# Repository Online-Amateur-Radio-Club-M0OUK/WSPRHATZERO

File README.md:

# WSPRHATZERO

This is the schematics and PCB design for a small (Pi Zero) format Pi Hat that can transmit WSPR.

Designed to use the [QRP Labs](https://www.qrp-labs.com/lpfkit.html) Low Pass Filter kits to allow for interchangable drop in boards for different bands.

You should hold an appropriate Amateur Radio License and be aware of the legalities of the band/frequency transmission rules for your region before using this board.

## Software

The defaults from [Wsprry Pi](https://wsprry-pi.readthedocs.io/en/latest/) should work with this project.

Pin settings:
* LED - GPIO18
* Power - GPIO19

## BOM Ordering

There is a [Mouser compatible BOM](./Mouser%20BOM.xls) included in this repository.

## Credits

The original project and schematic was [WSPR Without Tears](https://files.tapr.org/product_docs/WSPR/TAPR%20-%20WSPR%20Without%20Tears%20-%20v2.2.pdf) by TAPR.

* Original prototyping and testing Eoin M0NVK.
* Schematic transcription and PCB Layout by [Tom 2E0JJI](https://blog.howrandom.net).
* Project inspiration from Vic EI5IYB.

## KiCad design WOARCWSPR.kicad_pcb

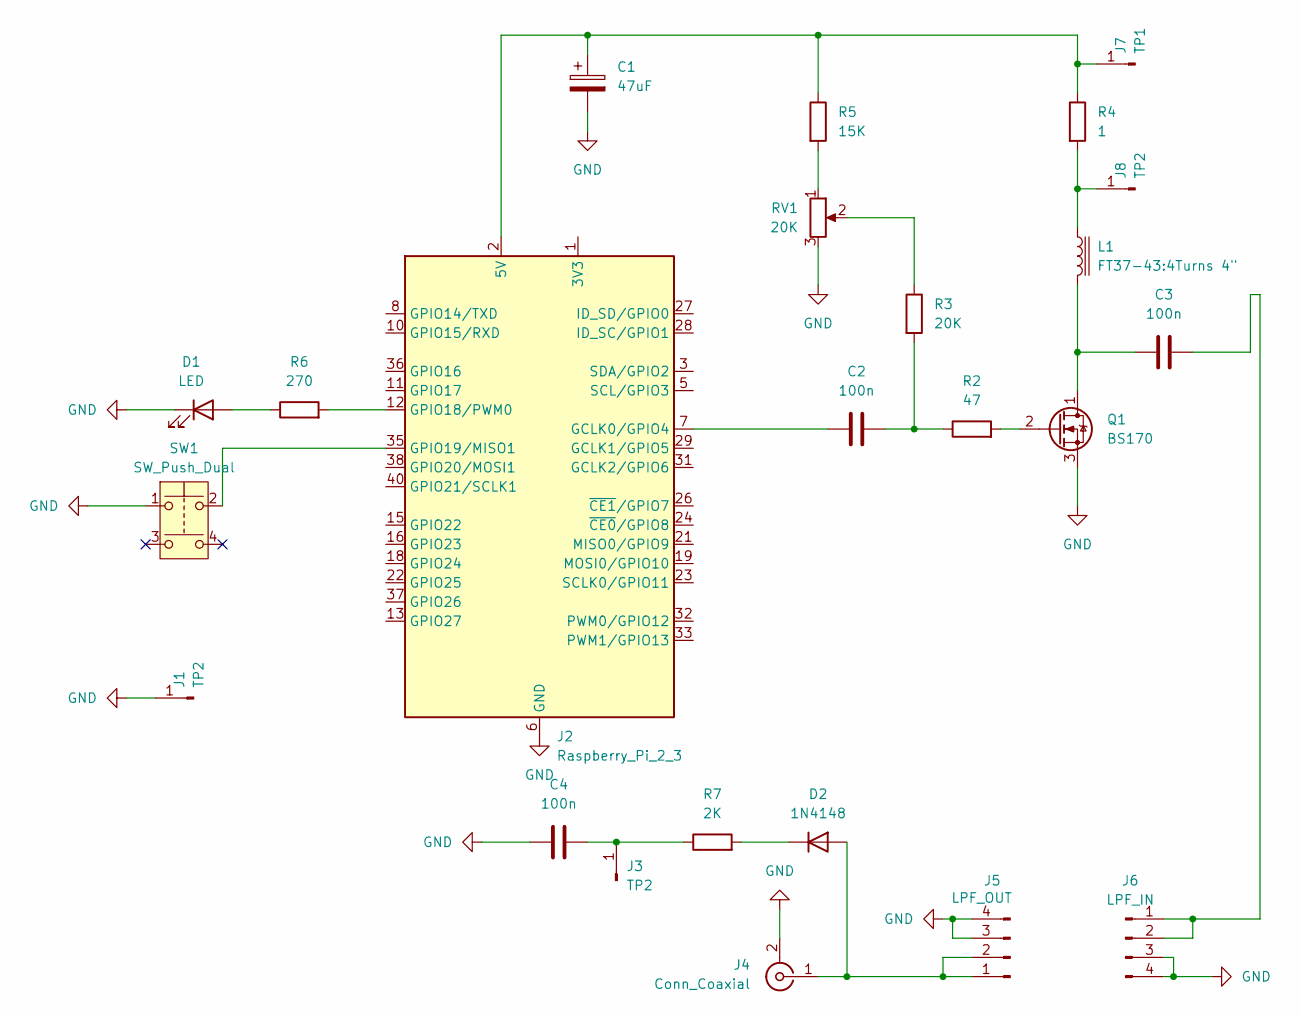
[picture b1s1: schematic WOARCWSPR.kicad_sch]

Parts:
C1: 47uF; CP_Radial_D5.0mm_P2.50mm
C2, C3, C4: 100n; C_Disc_D6.0mm_W2.5mm_P5.00mm
D1: LED; LED_D3.0mm
D2: 1N4148; D_DO-35_SOD27_P7.62mm_Horizontal
J1, J3, J8: TP2; PinHeader_1x01_P2.54mm_Vertical
J2: Raspberry_Pi_2_3; PinHeader_2x20_P2.54mm_Vertical
J4: Conn_Coaxial; SMA_Amphenol_132289_EdgeMount
J5: LPF_OUT; PinHeader_1x04_P2.54mm_Vertical
J6: LPF_IN; PinHeader_1x04_P2.54mm_Vertical
J7: TP1; PinHeader_1x01_P2.54mm_Vertical
L1: FT37-43:4Turns 4"; L_Axial_L9.5mm_D4.0mm_P15.24mm_Horizontal_Fastron_SMCC
Q1: BS170; TO-92_Inline
R2: 47; R_Axial_DIN0207_L6.3mm_D2.5mm_P7.62mm_Horizontal
R3: 20K; R_Axial_DIN0207_L6.3mm_D2.5mm_P7.62mm_Horizontal
R4: 1; R_Axial_DIN0207_L6.3mm_D2.5mm_P7.62mm_Horizontal
R5: 15K; R_Axial_DIN0207_L6.3mm_D2.5mm_P7.62mm_Horizontal
R6: 270; R_Axial_DIN0207_L6.3mm_D2.5mm_P7.62mm_Horizontal
R7: 2K; R_Axial_DIN0207_L6.3mm_D2.5mm_P7.62mm_Horizontal
RV1: 20K; Potentiometer_Piher_PT-6-V_Vertical
SW1: SW_Push_Dual; SW_PUSH_6mm

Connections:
GND: C1.2, C4.1, D1.1 (K), J1.1, J2.6 (GND), J2.9 (GND), J2.14 (GND), J2.20 (GND), J2.25 (GND), J2.30 (GND), J2.34 (GND), J2.39 (GND), J4.2 (Ext), J5.3, J5.4, J6.3, J6.4, Q1.3 (S), RV1.3, SW1.1
unnamed: C2.2, R2.1, R3.2
unnamed: D1.2 (A), R6.1
unnamed: D2.2 (A), J4.1 (In), J5.1, J5.2
unnamed: D2.1 (K), R7.2
unnamed: J2.1 (3V3), J2.17 (3V3)
unnamed: C2.1, J2.7 (GCLK0/GPIO4)
unnamed: J2.12 (GPIO18/PWM0), R6.2
unnamed: J2.35 (GPIO19/MISO1), SW1.2
unnamed: C4.2, J3.1, R7.1
unnamed: C3.2, J6.1, J6.2
unnamed: C1.1, J2.2 (5V), J2.4 (5V), J7.1, R4.1, R5.1
unnamed: J8.1, L1.1, R4.2
unnamed: C3.1, L1.2, Q1.1 (D)
unnamed: Q1.2 (G), R2.2
unnamed: R3.1, RV1.2
unnamed: R5.2, RV1.1

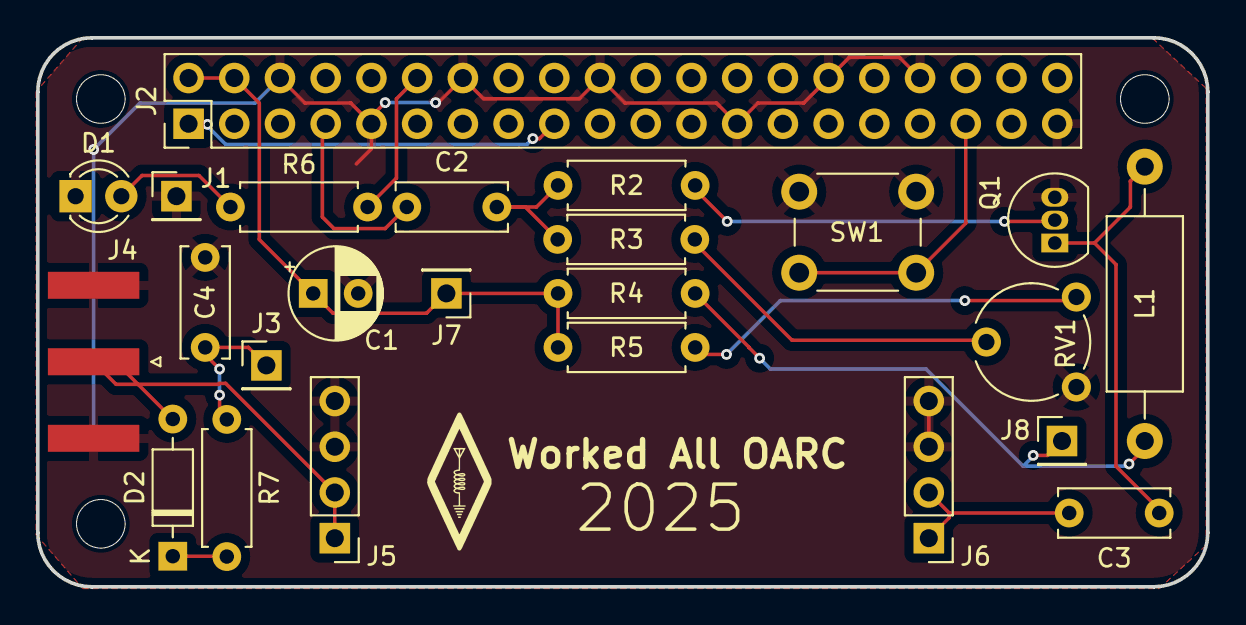
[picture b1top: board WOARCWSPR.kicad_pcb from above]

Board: 2 copper layers, 65.0 x 30.5 mm, 24 parts (0 on the bottom side), 17 nets.

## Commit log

2025-06-24 Initial transcribed schematic
2025-07-06 V1.0
2025-07-06 Correct pin layout for filter board
2025-07-06 Change to ceramic cap footprints
2025-07-06 Swap to 3mm THT LED
2025-07-06 Make J7 routing prettier
2025-07-06 Update SMA footprint for correct size of connector
2025-07-15 Update with V1.1 gerber
2025-07-20 Add initial README and BOM
